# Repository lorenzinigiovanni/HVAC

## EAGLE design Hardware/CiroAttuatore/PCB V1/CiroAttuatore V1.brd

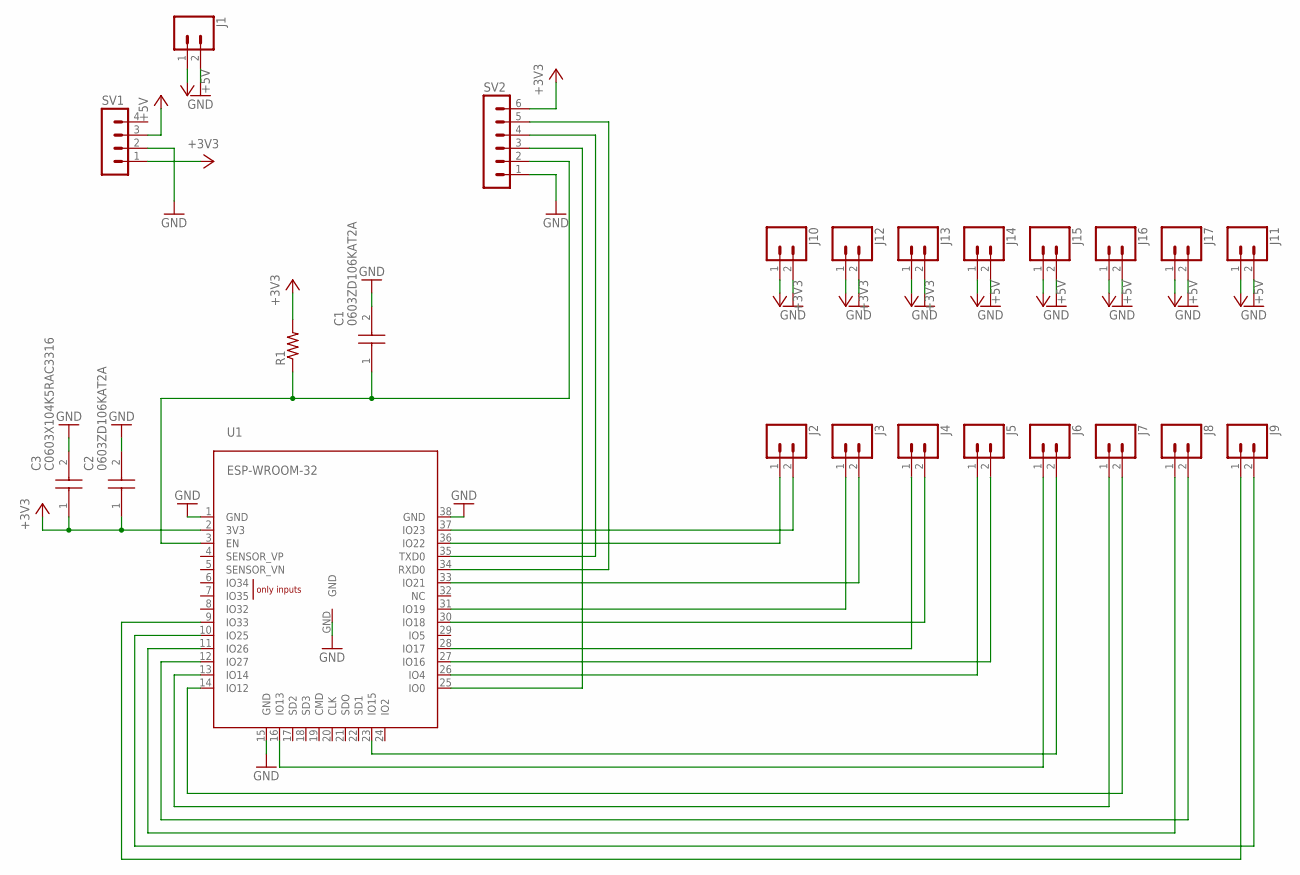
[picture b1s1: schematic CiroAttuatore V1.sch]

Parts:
C1, C2: 0603ZD106KAT2A; CAPC1608X90N
C3: C0603X104K5RAC3316; CAPC1608X95N
J1, J2, J3, J4, J5, J6, J7, J8, J9, J10, J11, J12, J13, J14, J15, J16, J17: CONN_025MM; SCREWTERMINAL-5MM-2
R1: R-US_R0603; R0603
SV1: MA04-1
SV2: MA06-1
U1: ESP-WROOM-32

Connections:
+3V3: C2.1, C3.1, J10.1, J12.1, J13.1, R1.2, SV1.1, SV2.6, U1.2 (3V3)
+5V: J1.1, J11.1, J14.1, J15.1, J16.1, J17.1, SV1.3
GND: C1.2, C2.2, C3.2, J1.2, J10.2, J11.2, J12.2, J13.2, J14.2, J15.2, J16.2, J17.2, SV1.2, SV2.1, U1.1 (GND), U1.15 (GND), U1.38 (GND), U1.GND
unnamed: J2.2, U1.37 (IO23)
unnamed: J2.1, U1.36 (IO22)
unnamed: J3.2, U1.33 (IO21)
unnamed: SV2.4, U1.35 (TXD0)
unnamed: SV2.5, U1.34 (RXD0)
unnamed: SV2.3, U1.25 (IO0)
unnamed: C1.1, R1.1, SV2.2, U1.3 (EN)
unnamed: J3.1, U1.31 (IO19)
unnamed: J4.2, U1.30 (IO18)
unnamed: J4.1, U1.28 (IO17)
unnamed: J5.2, U1.27 (IO16)
unnamed: J5.1, U1.26 (IO4)
unnamed: J6.2, U1.23 (IO15)
unnamed: J6.1, U1.16 (IO13)
unnamed: J7.2, U1.14 (IO12)
unnamed: J7.1, U1.13 (IO14)
unnamed: J8.2, U1.12 (IO27)
unnamed: J8.1, U1.11 (IO26)
unnamed: J9.2, U1.10 (IO25)
unnamed: J9.1, U1.9 (IO33)

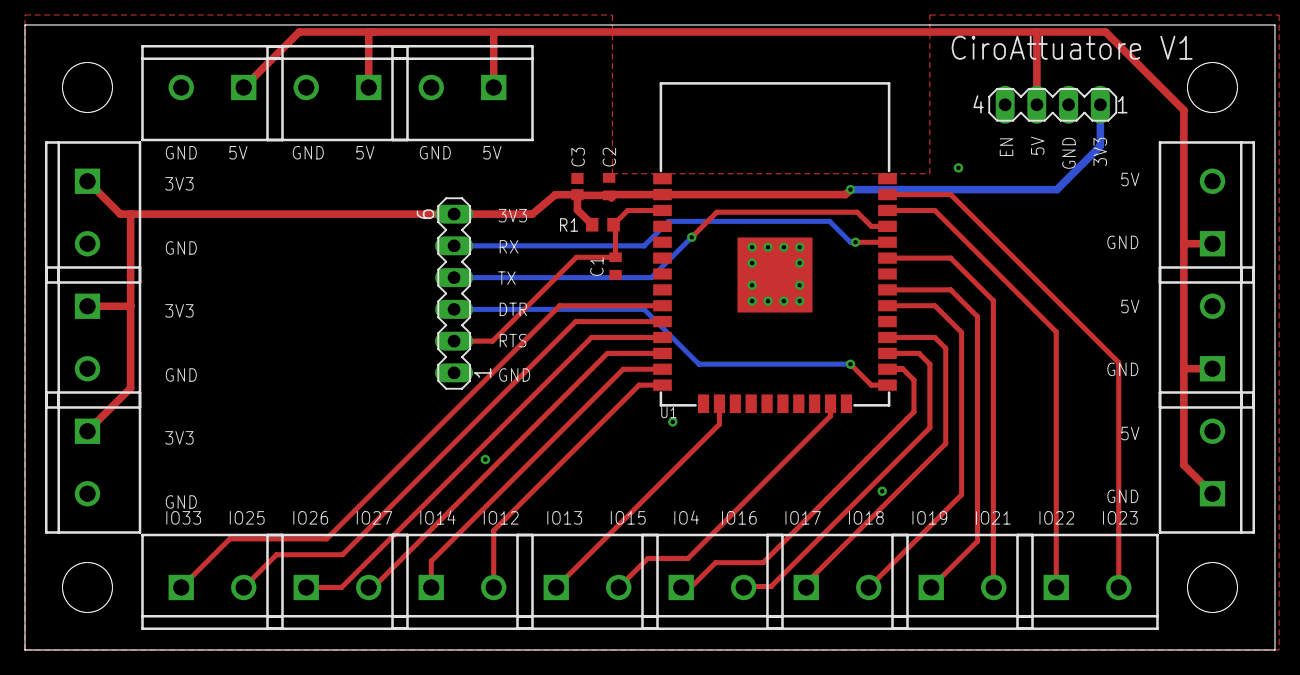
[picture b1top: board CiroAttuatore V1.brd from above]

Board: 2 copper layers, 100.0 x 50.0 mm, 24 parts (0 on the bottom side), 23 nets.

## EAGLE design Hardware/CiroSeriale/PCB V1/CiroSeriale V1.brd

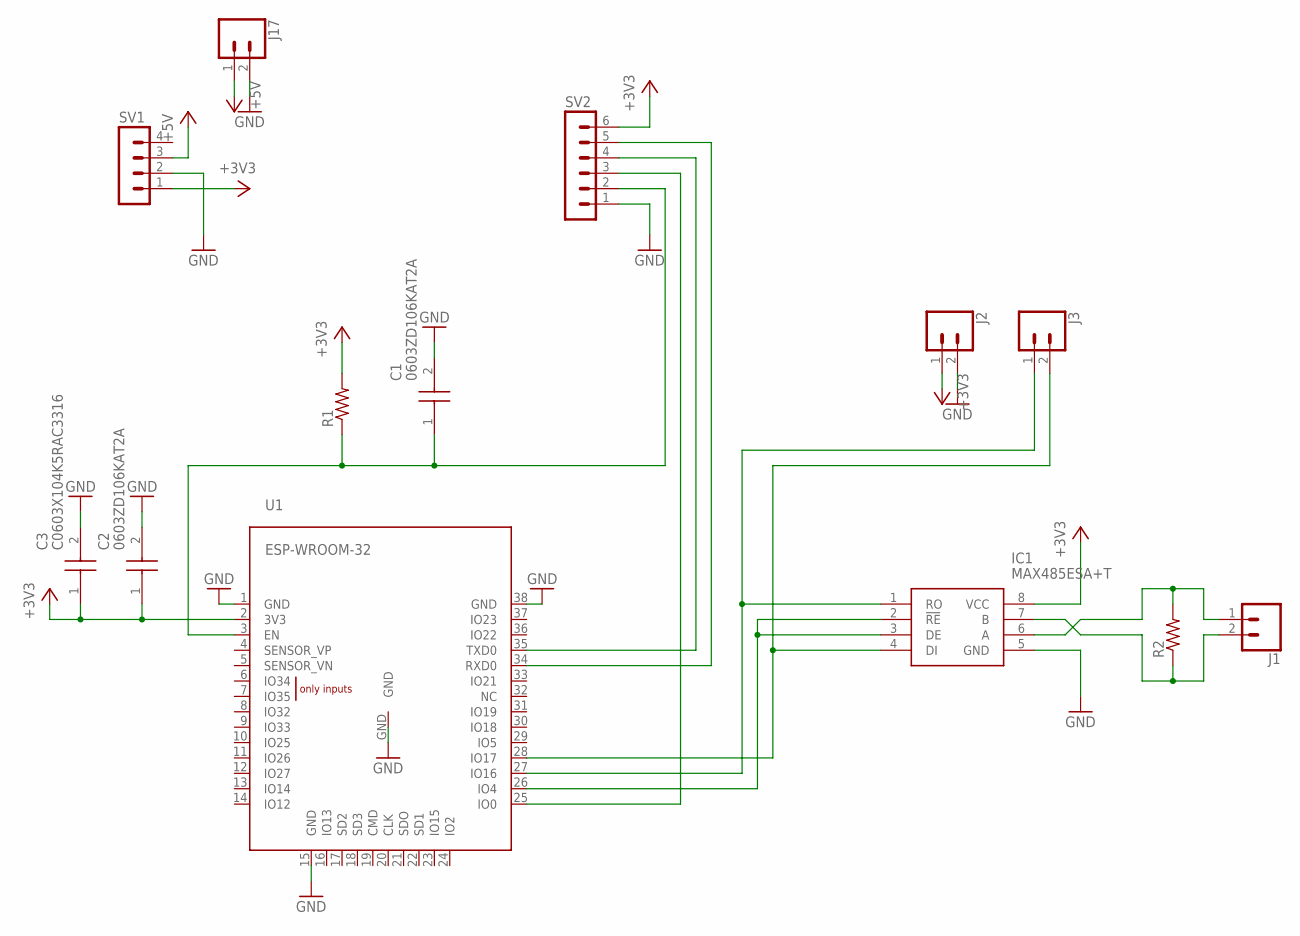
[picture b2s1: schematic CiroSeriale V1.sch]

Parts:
C1, C2: 0603ZD106KAT2A; CAPC1608X90N
C3: C0603X104K5RAC3316; CAPC1608X95N
IC1: MAX485ESA+T; SOIC127P600X175-8N
J1, J2, J3, J17: CONN_025MM; SCREWTERMINAL-5MM-2
R1: R-US_R0603; R0603
R2: R-US_0204/7; 0204/7
SV1: MA04-1
SV2: MA06-1
U1: ESP-WROOM-32

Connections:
+3V3: C2.1, C3.1, IC1.8 (VCC), J2.1, R1.2, SV1.1, SV2.6, U1.2 (3V3)
+5V: J17.1, SV1.3
GND: C1.2, C2.2, C3.2, IC1.5 (GND), J2.2, J17.2, SV1.2, SV2.1, U1.1 (GND), U1.15 (GND), U1.38 (GND), U1.GND
unnamed: IC1.4 (DI), J3.2, U1.28 (IO17)
unnamed: IC1.1 (RO), J3.1, U1.27 (IO16)
unnamed: IC1.6 (A), J1.1, R2.2
unnamed: IC1.7 (B), J1.2, R2.1
unnamed: SV2.4, U1.35 (TXD0)
unnamed: SV2.5, U1.34 (RXD0)
unnamed: SV2.3, U1.25 (IO0)
unnamed: C1.1, R1.1, SV2.2, U1.3 (EN)
unnamed: IC1.2 (!RE), IC1.3 (DE), U1.26 (IO4)

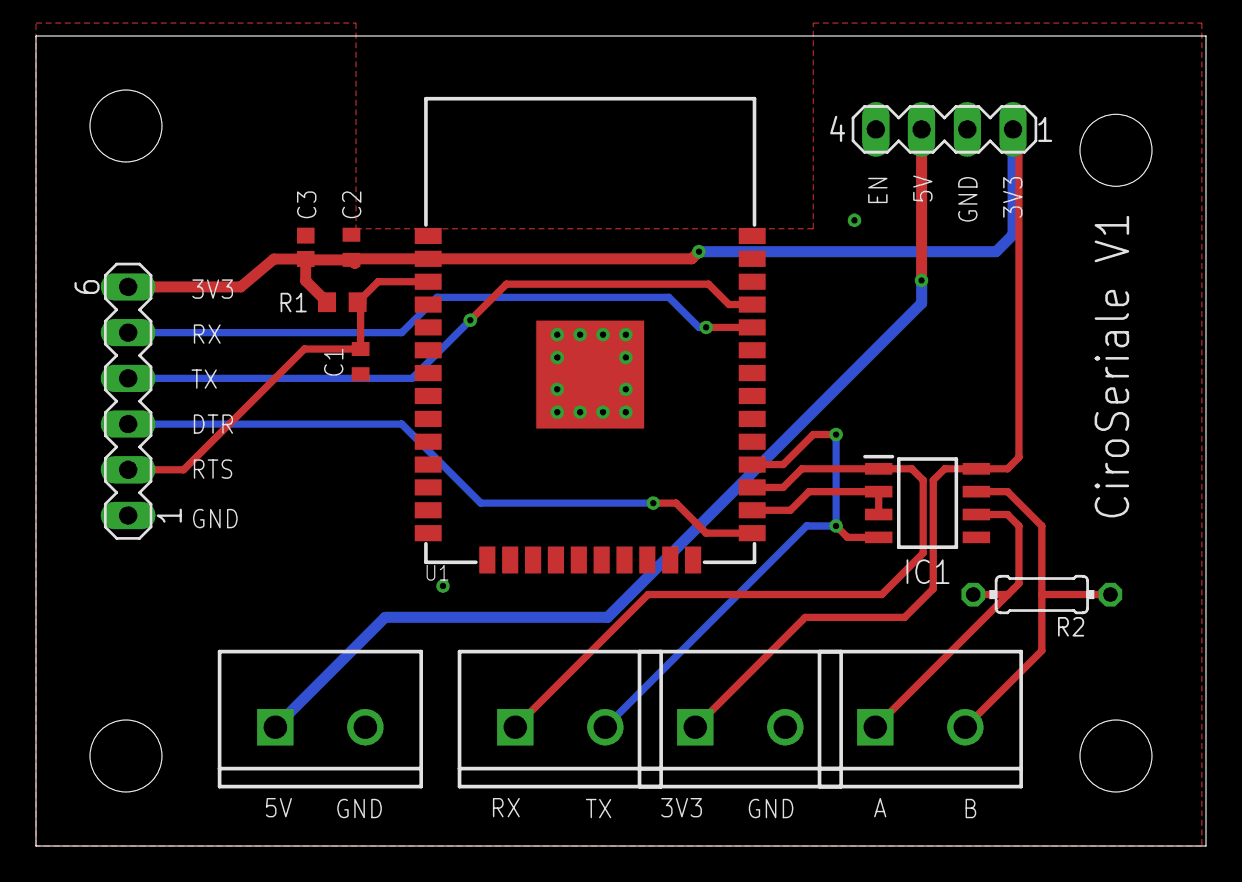
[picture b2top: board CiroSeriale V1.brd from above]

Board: 2 copper layers, 65.0 x 45.0 mm, 13 parts (0 on the bottom side), 12 nets.

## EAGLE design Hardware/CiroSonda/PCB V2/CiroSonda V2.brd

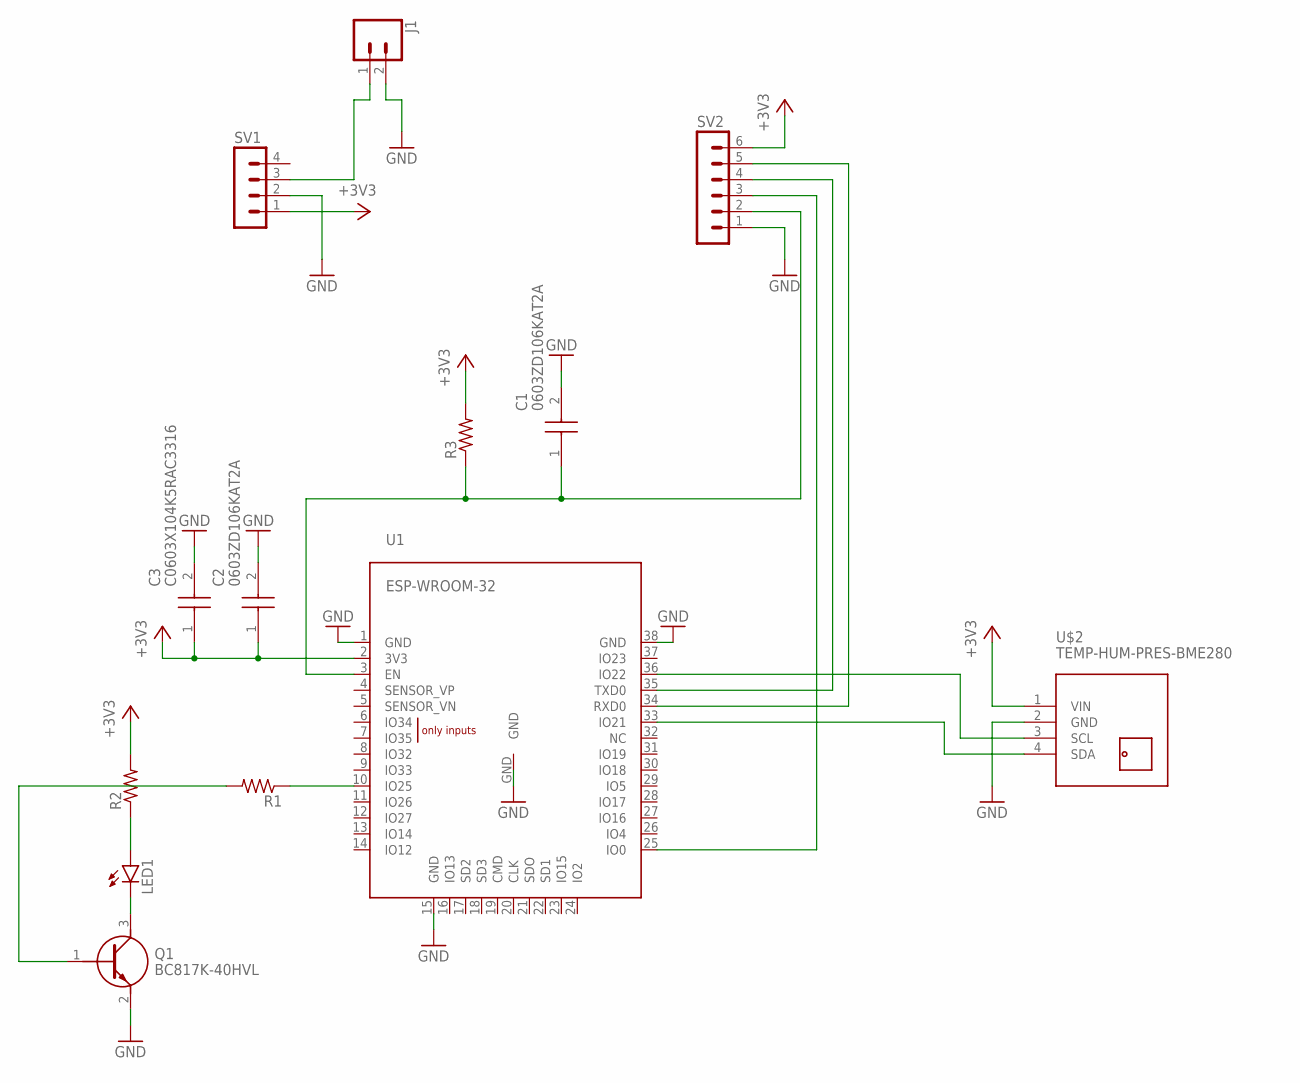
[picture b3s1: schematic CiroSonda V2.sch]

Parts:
C1, C2: 0603ZD106KAT2A; CAPC1608X90N
C3: C0603X104K5RAC3316; CAPC1608X95N
J1: CONN_025MM; SCREWTERMINAL-5MM-2
LED1: LED5MM
Q1: BC817K-40HVL; SOT95P230X110-3N
R1, R3: R-US_R0603; R0603
R2: R-US_R0805; R0805
SV1: MA04-1
SV2: MA06-1
U1: ESP-WROOM-32
U$2: TEMP-HUM-PRES-BME280

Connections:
+3V3: C2.1, C3.1, R2.2, R3.2, SV1.1, SV2.6, U1.2 (3V3), U$2.1 (VIN)
GND: C1.2, C2.2, C3.2, J1.2, Q1.2 (E), SV1.2, SV2.1, U1.1 (GND), U1.15 (GND), U1.38 (GND), U1.GND, U$2.2 (GND)
unnamed: U1.36 (IO22), U$2.3 (SCL)
unnamed: U1.33 (IO21), U$2.4 (SDA)
unnamed: LED1.A, R2.1
unnamed: J1.1, SV1.3
unnamed: SV2.4, U1.35 (TXD0)
unnamed: SV2.5, U1.34 (RXD0)
unnamed: SV2.3, U1.25 (IO0)
unnamed: C1.1, R3.1, SV2.2, U1.3 (EN)
unnamed: R1.1, U1.10 (IO25)
unnamed: LED1.K (C), Q1.3 (C)
unnamed: Q1.1 (B), R1.2

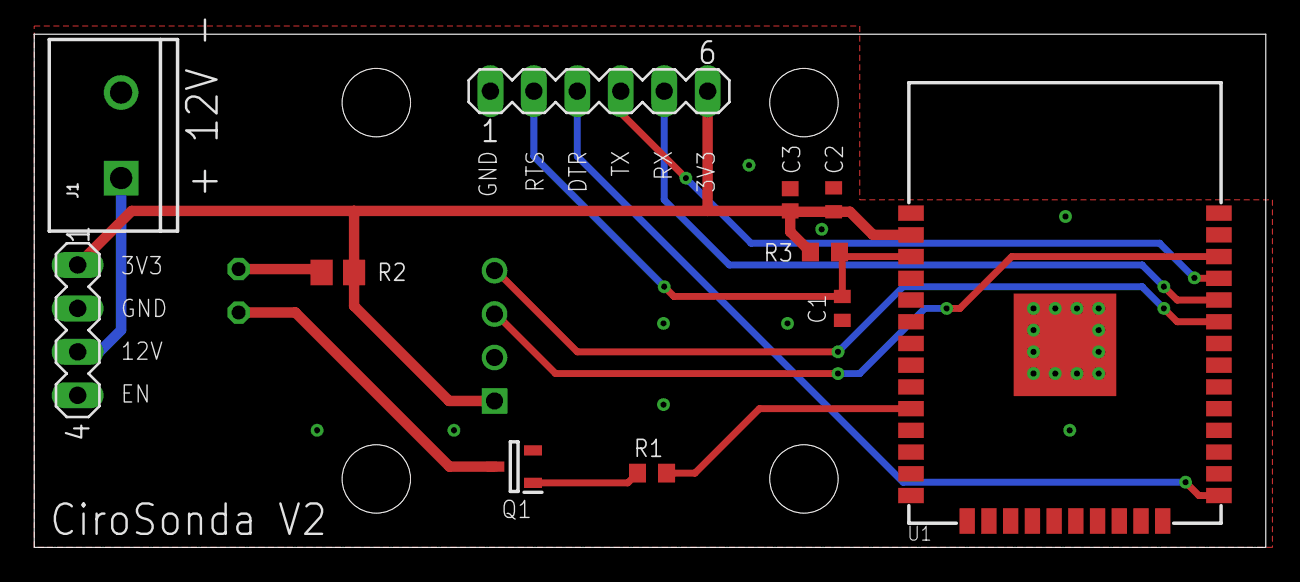
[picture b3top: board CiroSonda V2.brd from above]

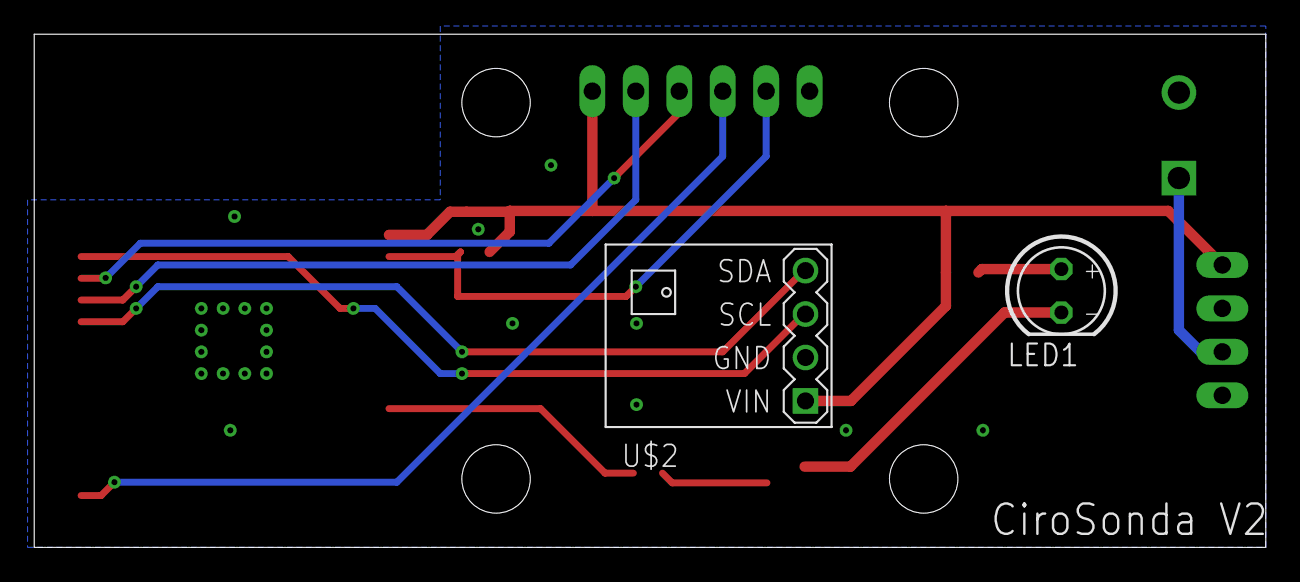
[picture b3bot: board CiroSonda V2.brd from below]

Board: 2 copper layers, 72.0 x 30.0 mm, 13 parts (2 on the bottom side), 13 nets.

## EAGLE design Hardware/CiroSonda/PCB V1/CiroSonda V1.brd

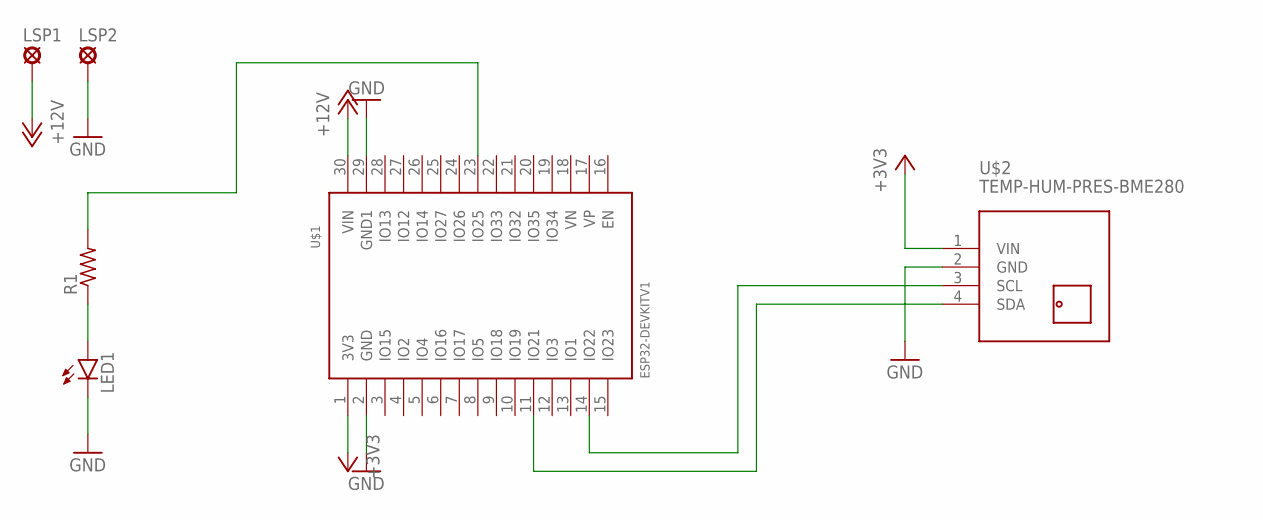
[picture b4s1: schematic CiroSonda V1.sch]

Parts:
LED1: LED5MM
LSP1, LSP2: LSP11
R1: R-US_0204/7; 0204/7
U$1: ESP32DEVKITV1; ESP32-DEVKITV1
U$2: TEMP-HUM-PRES-BME280

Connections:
+3V3: U$1.1 (3V3), U$2.1 (VIN)
+12V: LSP1.MP, U$1.30 (VIN)
GND: LED1.K (C), LSP2.MP, U$1.2 (GND), U$1.29 (GND1), U$2.2 (GND)
unnamed: U$1.11 (IO21), U$2.4 (SDA)
unnamed: U$1.14 (IO22), U$2.3 (SCL)
unnamed: LED1.A, R1.1
unnamed: R1.2, U$1.23 (IO25)

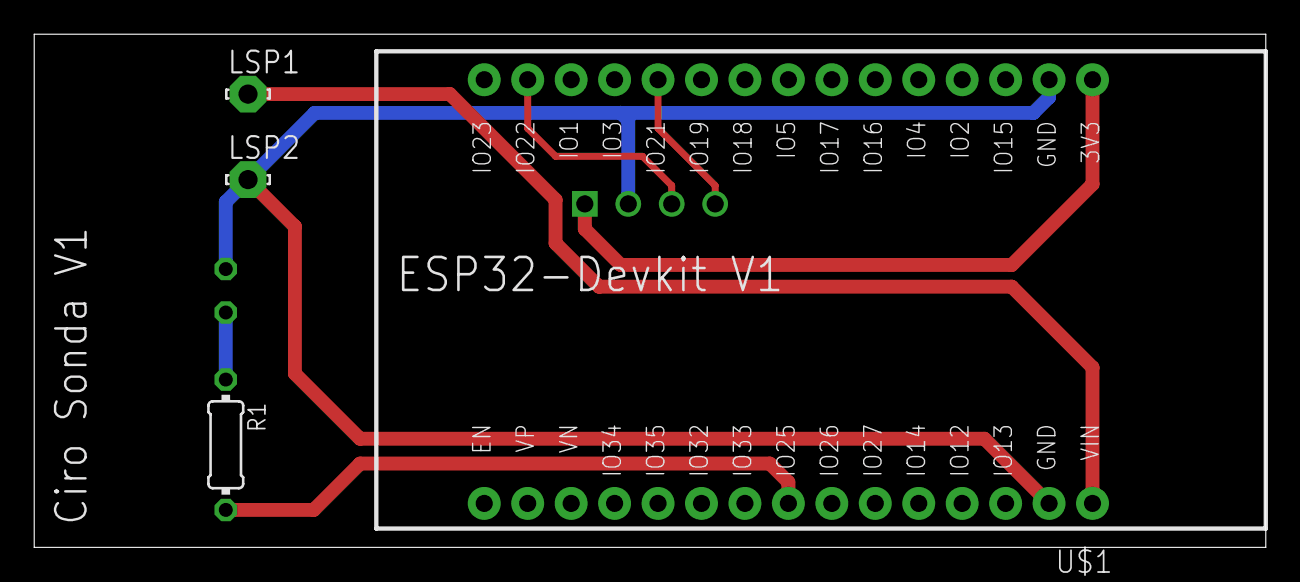
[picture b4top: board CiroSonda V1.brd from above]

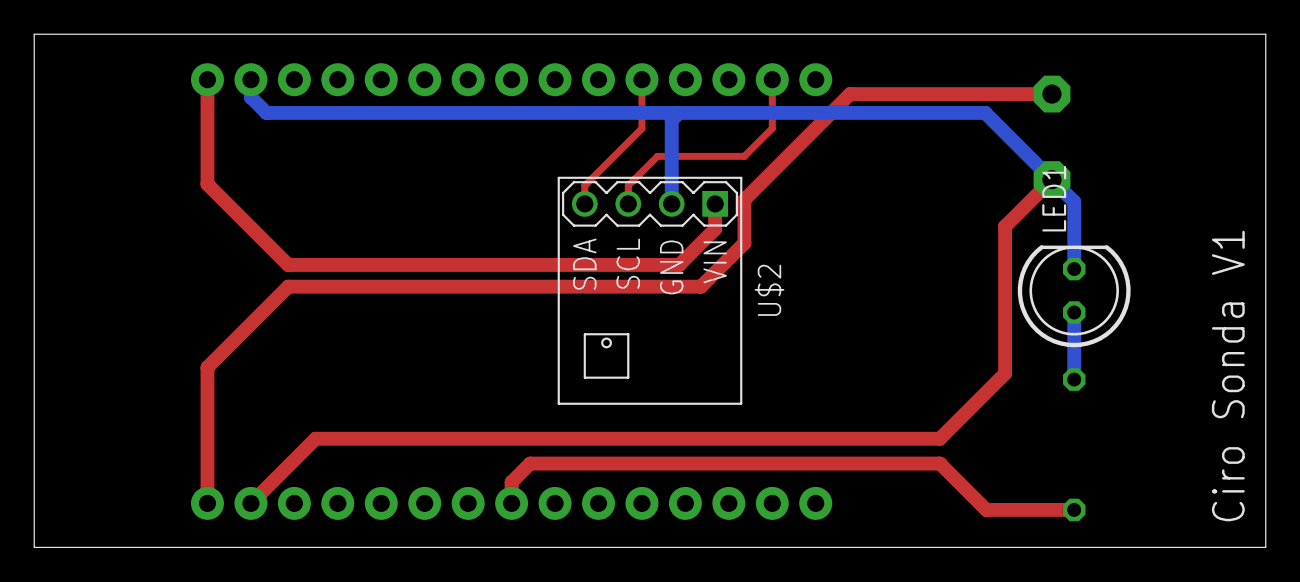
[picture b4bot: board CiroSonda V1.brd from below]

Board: 2 copper layers, 72.0 x 30.0 mm, 6 parts (2 on the bottom side), 7 nets.

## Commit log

2019-12-11 Create CiroSonda hardware
2019-12-11 Create CiroAttuatore software
2019-12-11 Create CiroSonda software
2019-12-11 Create Controller software
2019-12-12 Change sensor type to BME280
2019-12-12 Create homekit sensor accessory
2019-12-12 Add IR trasmitter software for LG AC
2019-12-13 Create library for LG air conditioner
2019-12-13 Bug fix in LG IR code
2019-12-13 Bug fix in LG IR and add print function
2019-12-13 Add mqtt to test the IR from remote
2019-12-13 Add Aircon class
2019-12-14 Fix import
2019-12-14 Fix mqtt payload
2019-12-14 Update IR
2019-12-14 Update AC
2019-12-14 Add AC IR
2019-12-29 Change Room class
2019-12-29 Global mqtt and homekit variables
2019-12-30 Move room file
2019-12-30 Add outdoors class
2019-12-30 Add \n
2019-12-30 Update homekit accessories
2019-12-30 Lowercase and without spaces mqtt topics
2019-12-30 Private methods
2019-12-30 Add events for AmbientSensor
2019-12-30 Use AmbientSensor events in Outdoors
2019-12-30 Aggiornati nomi dispositivi
2019-12-30 Nome dispositivi homekit in italiano
2019-12-30 Modify HomekitTemperatureSensor limits
2019-12-30 Add support to room without an heating system
2020-01-01 Add climatic regulator
2020-01-01 Use event in AmbientTemperatureController
2020-01-24 New hardware
2020-02-05 Update LG aircon control software
2020-02-17 Fix ac topic and ir led transistor
2020-02-23 Remove air conditioner code
2023-03-02 Bump minimist and mkdirp in /Software/Controller
    Bumps [minimist](https://github.com/minimistjs/minimist) and [mkdirp](https://github.com/isaacs/node-mkdirp). These dependencies needed to be updated together.
    Updates `minimist` from 1.2.0 to 1.2.8
    - [Release notes](https://github.com/minimistjs/minimist/releases)
    - [Changelog](https://github.com/minimistjs/minimist/blob/main/CHANGELOG.md)
    - [Commits](https://github.com/minimistjs/minimist/compare/v1.2.0...v1.2.8)
    Updates `mkdirp` from 0.5.1 to 0.5.6
2023-03-02 Bump dns-packet and multicast-dns in /Software/Controller
    Bumps [dns-packet](https://github.com/mafintosh/dns-packet) and [multicast-dns](https://github.com/mafintosh/multicast-dns). These dependencies needed to be updated together.
    Updates `dns-packet` from 4.2.0 to 5.4.0
    - [Release notes](https://github.com/mafintosh/dns-packet/releases)
    - [Changelog](https://github.com/mafintosh/dns-packet/blob/master/CHANGELOG.md)
    - [Commits](https://github.com/mafintosh/dns-packet/compare/v4.2.0...5.4.0)
    Updates `multicast-dns` from 7.2.0 to 7.2.5
2023-05-07 Bump bl from 1.2.2 to 1.2.3 in /Software/Controller
    Bumps [bl](https://github.com/rvagg/bl) from 1.2.2 to 1.2.3.
    - [Release notes](https://github.com/rvagg/bl/releases)
    - [Changelog](https://github.com/rvagg/bl/blob/master/CHANGELOG.md)
    - [Commits](https://github.com/rvagg/bl/compare/v1.2.2...v1.2.3)
    ---
    updated-dependencies:
2023-05-07 Bump minimatch from 3.0.4 to 3.1.2 in /Software/Controller
    Bumps [minimatch](https://github.com/isaacs/minimatch) from 3.0.4 to 3.1.2.
    - [Changelog](https://github.com/isaacs/minimatch/blob/main/changelog.md)
    - [Commits](https://github.com/isaacs/minimatch/compare/v3.0.4...v3.1.2)
    ---
    updated-dependencies:
    - dependency-name: minimatch
2023-05-07 Bump glob-parent and mqtt in /Software/Controller
    Removes [glob-parent](https://github.com/gulpjs/glob-parent). It's no longer used after updating ancestor dependency [mqtt](https://github.com/mqttjs/MQTT.js). These dependencies need to be updated t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
    Removes `glob-parent`
    Updates `mqtt` from 3.0.0 to 4.3.7
    - [Release notes](https://github.com/mqttjs/MQTT.js/releases)
    - [Changelog](https://github.com/mqttjs/MQTT.js/blob/main/CHANGELOG.md)
    - [Commits](https://github.com/mqttjs/MQTT.js/compare/v3.0.0...v4.3.7)

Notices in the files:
parts and their libraries:
SparkFun-Connectors: Licensing: Creative Commons ShareAlike 4.0 International - https://creativecommons.org/licenses/by-sa/4.0
diy-modules: Released under the Creative Commons Attribution 4.0 International License: http://creativecommons.org/licenses/by/4.0
